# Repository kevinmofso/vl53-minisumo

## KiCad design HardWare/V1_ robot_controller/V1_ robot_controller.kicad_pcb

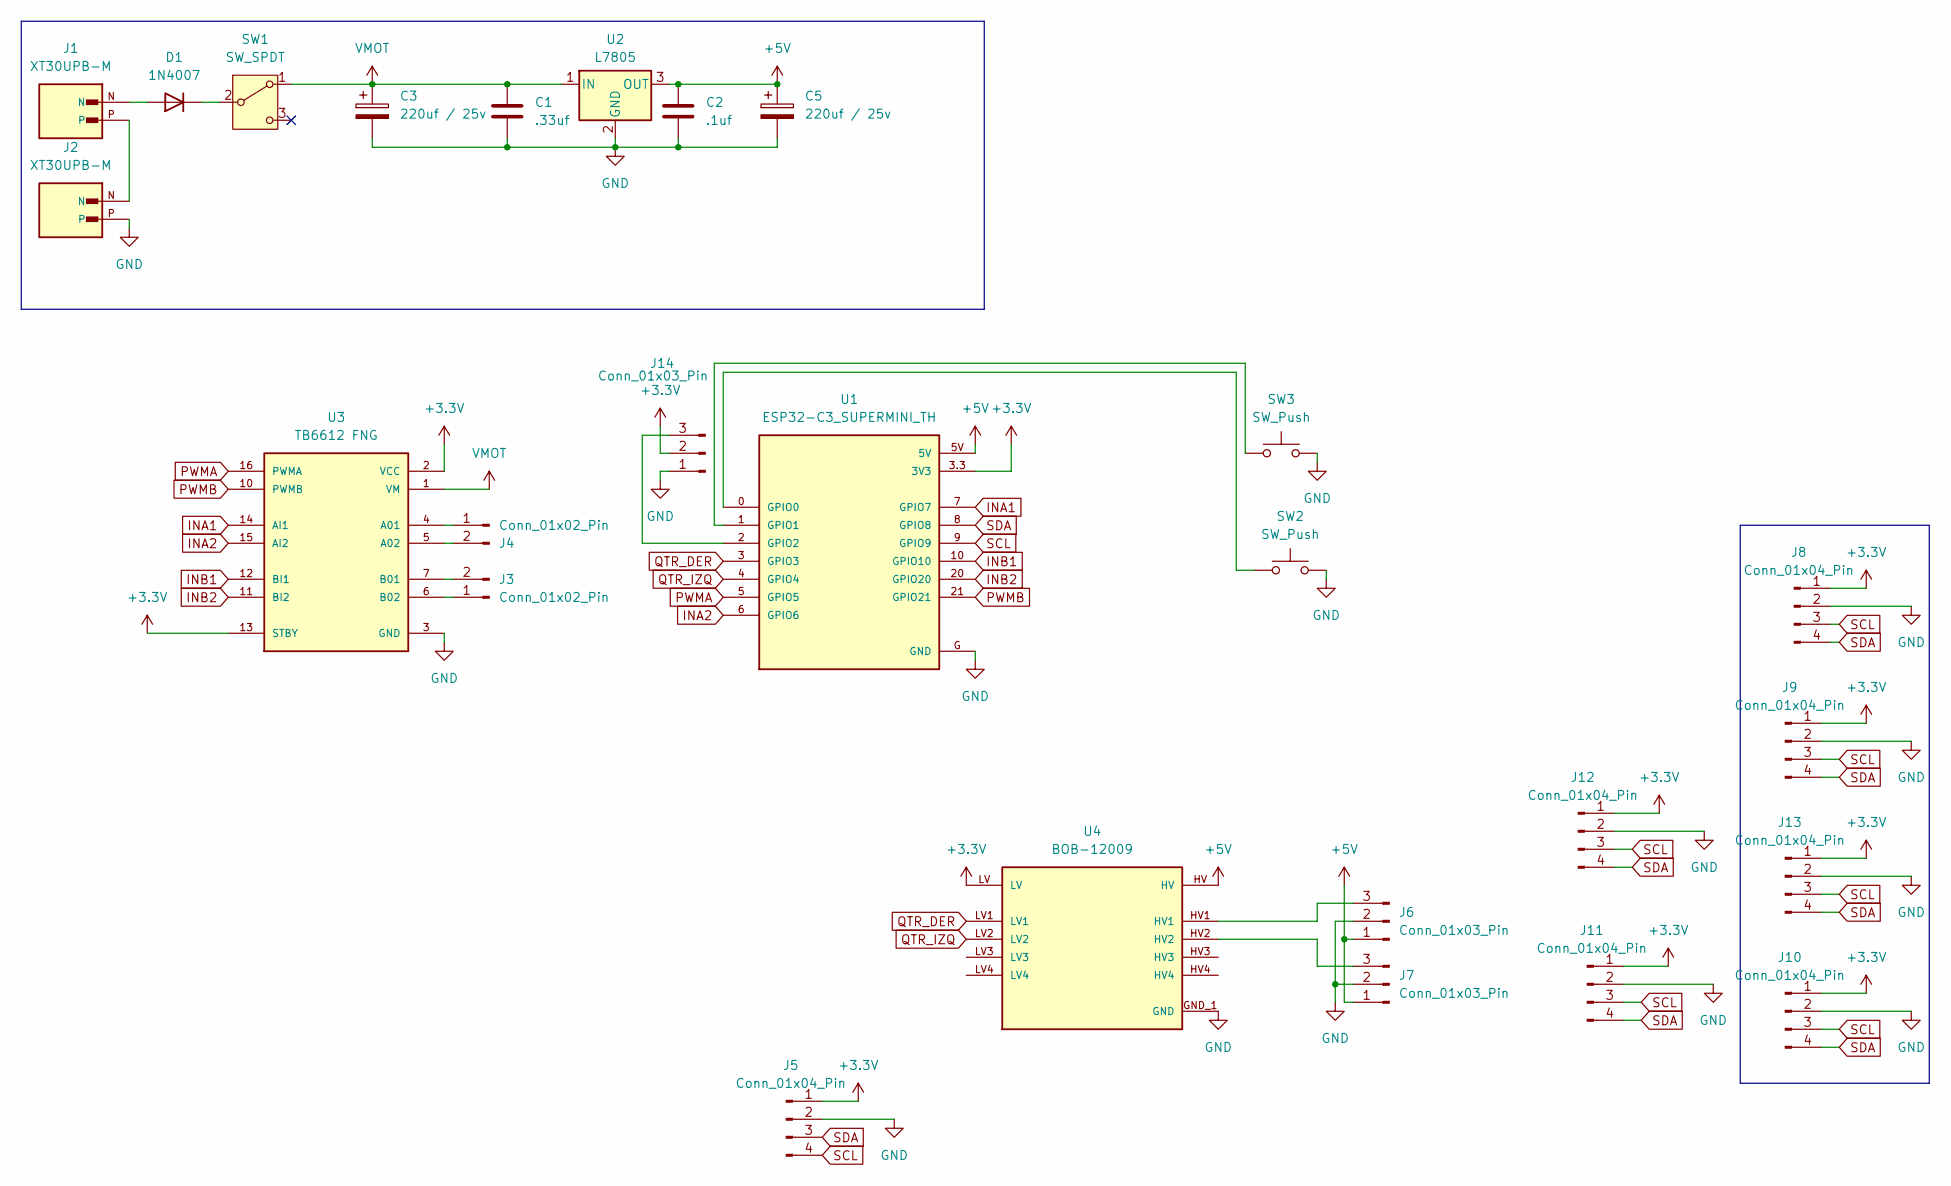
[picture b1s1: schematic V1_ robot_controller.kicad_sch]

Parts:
C1: .33uf; C_Disc_D3.0mm_W2.0mm_P2.50mm
C2: .1uf; C_Disc_D3.0mm_W2.0mm_P2.50mm
C3, C5: 220uf / 25v; CP_Radial_D6.3mm_P2.50mm
D1: 1N4007; D_DO-41_SOD81_P10.16mm_Horizontal
J1, J2: XT30UPB-M; AMASS_XT30UPB-M
J3, J4: Conn_01x02_Pin; Molex_KK-254_AE-6410-02A_1x02_P2.54mm_Vertical
J5, J8, J9, J10, J11, J12, J13: Conn_01x04_Pin; PinHeader_1x04_P2.54mm_Vertical
J6, J7, J14: Conn_01x03_Pin; PinHeader_1x03_P2.54mm_Vertical
SW1: SW_SPDT; SW_Slide_SPDT_Straight_CK_OS102011MS2Q
SW2, SW3: SW_Push; SW_PUSH_6mm_H4.3mm
U1: ESP32-C3_SUPERMINI_TH; MODULE_ESP32-C3_SUPERMINI_TH
U2: L7805; TO-220F-3_Horizontal_TabUp
U3: TB6612 FNG; MODULE_ROB-14450; PARTREV 11-13-17
U4: BOB-12009; CONV_BOB-12009; PARTREV 01

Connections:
+3.3V: J5.1, J8.1, J9.1, J10.1, J11.1, J12.1, J13.1, J14.2, U1.3.3 (3V3), U3.2 (VCC), U3.13 (STBY), U4.LV
+5V: C2.1, C5.1, J6.1, J7.1, U1.5V, U2.3 (OUT), U4.HV
GND: C1.2, C2.2, C3.2, C5.2, J2.P, J5.2, J6.2, J7.2, J8.2, J9.2, J10.2, J11.2, J12.2, J13.2, J14.1, SW2.1, SW3.1, U1.G (GND), U2.2 (GND), U3.3 (GND), U3.8 (GND), U3.9 (GND), U4.GND_1 (GND), U4.GND_2 (GND)
INA1: U1.7 (GPIO7), U3.14 (AI1)
INA2: U1.6 (GPIO6), U3.15 (AI2)
INB1: U1.10 (GPIO10), U3.12 (BI1)
INB2: U1.20 (GPIO20), U3.11 (BI2)
unnamed: D1.2 (A), J1.N
unnamed: D1.1 (K), SW1.2 (B)
unnamed: J1.P, J2.N
unnamed: J3.1, U3.6 (B02)
unnamed: J3.2, U3.7 (B01)
unnamed: J4.1, U3.4 (A01)
unnamed: J4.2, U3.5 (A02)
unnamed: J6.3, U4.HV1
unnamed: J7.3, U4.HV2
unnamed: J14.3, U1.2 (GPIO2)
unnamed: SW2.2, U1.0 (GPIO0)
unnamed: SW3.2, U1.1 (GPIO1)
PWMA: U1.5 (GPIO5), U3.16 (PWMA)
PWMB: U1.21 (GPIO21), U3.10 (PWMB)
QTR_DER: U1.3 (GPIO3), U4.LV1
QTR_IZQ: U1.4 (GPIO4), U4.LV2
SCL: J5.4, J8.3, J9.3, J10.3, J11.3, J12.3, J13.3, U1.9 (GPIO9)
SDA: J5.3, J8.4, J9.4, J10.4, J11.4, J12.4, J13.4, U1.8 (GPIO8)
VMOT: C1.1, C3.1, SW1.1 (A), U2.1 (IN), U3.1 (VM)

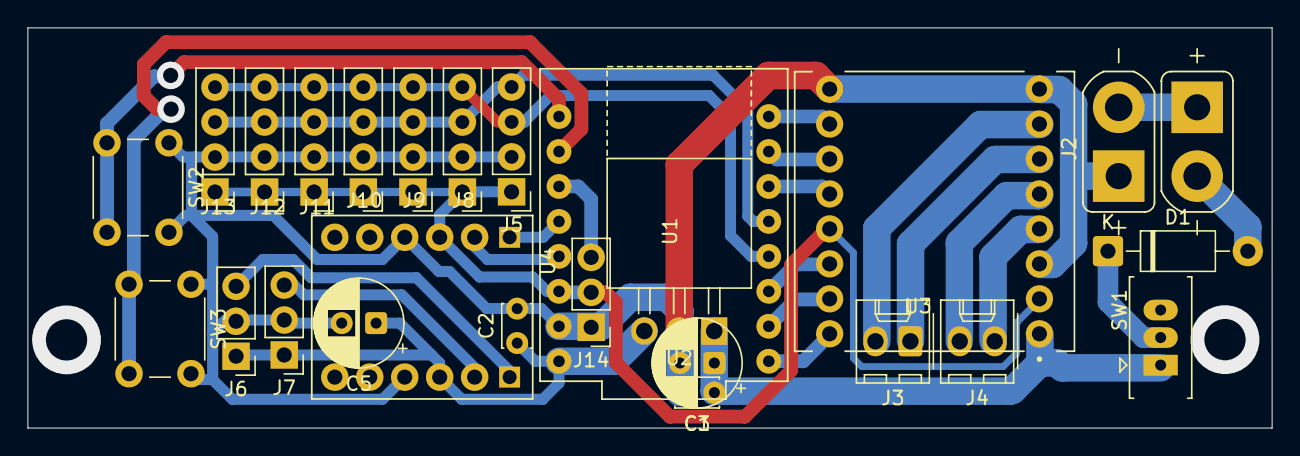
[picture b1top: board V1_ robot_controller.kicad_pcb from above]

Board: 2 copper layers, 90.4 x 29.1 mm, 26 parts (0 on the bottom side), 26 nets.

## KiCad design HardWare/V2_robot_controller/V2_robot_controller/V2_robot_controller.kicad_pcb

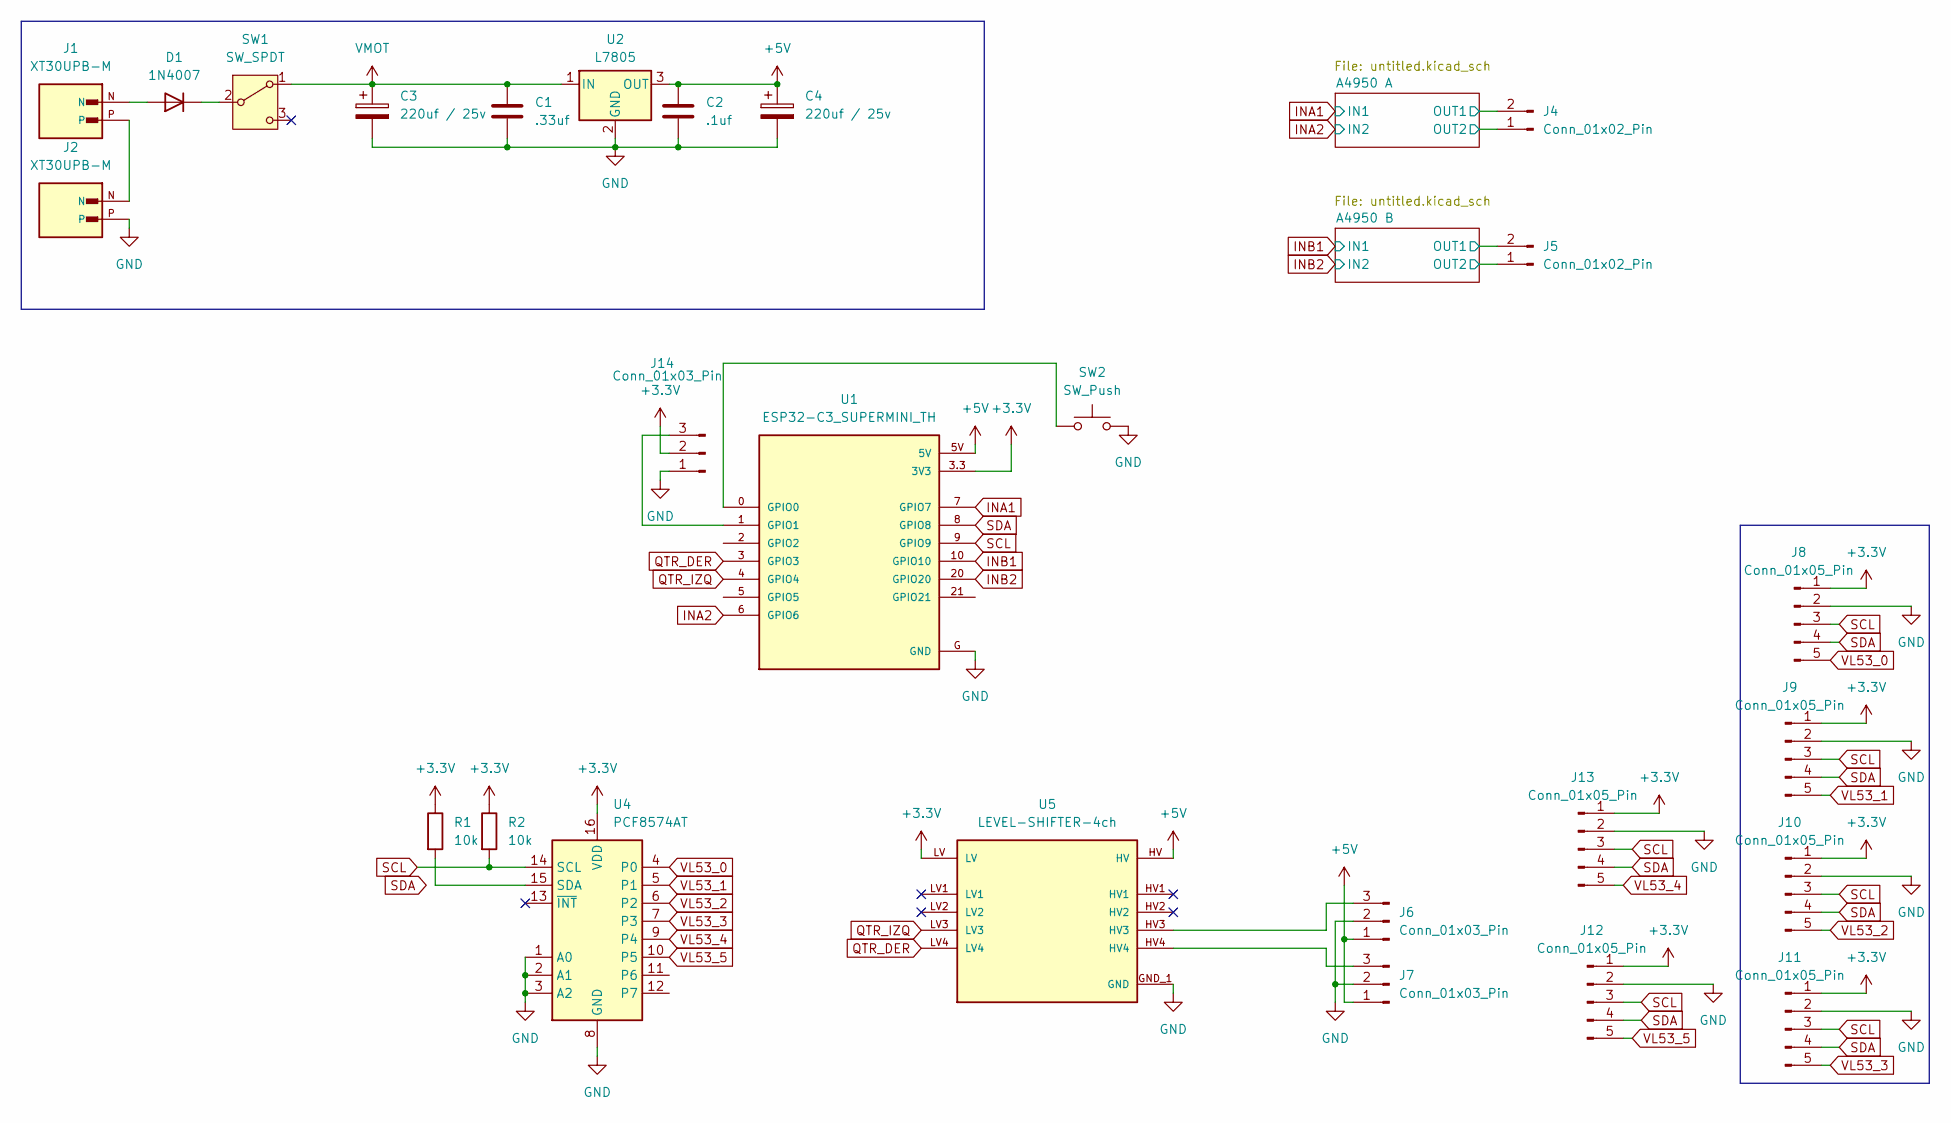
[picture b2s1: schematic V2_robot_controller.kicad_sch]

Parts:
C1: .33uf; C_Disc_D3.0mm_W2.0mm_P2.50mm
C2: .1uf; C_Disc_D3.0mm_W2.0mm_P2.50mm
C3: 220uf / 25v; CP_Radial_D6.3mm_P2.50mm
C4: 220uf / 25v; CP_Radial_D8.0mm_P3.80mm
D1: 1N4007; D_DO-41_SOD81_P10.16mm_Horizontal
J1, J2: XT30UPB-M; AMASS_XT30UPB-M
J4, J5: Conn_01x02_Pin; Molex_KK-254_AE-6410-02A_1x02_P2.54mm_Vertical
J6, J7, J14: Conn_01x03_Pin; PinHeader_1x03_P2.54mm_Vertical
J8, J9, J10, J11, J12, J13: Conn_01x05_Pin; PinHeader_1x05_P2.54mm_Vertical
R1, R2: 10k; R_0805_2012Metric_Pad1.20x1.40mm_HandSolder
SW1: SW_SPDT; SW_Slide_SPDT_Straight_CK_OS102011MS2Q
SW2: SW_Push; SW_PUSH_6mm_H4.3mm
U1: ESP32-C3_SUPERMINI_TH; MODULE_ESP32-C3_SUPERMINI_TH
U2: L7805; TO-220F-3_Horizontal_TabUp
U4: PCF8574AT; SOIC-16W_7.5x10.3mm_P1.27mm
U5: LEVEL-SHIFTER-4ch; CONV_BOB-12009; PARTREV 01

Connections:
+3.3V: J8.1, J9.1, J10.1, J11.1, J12.1, J13.1, J14.2, R1.1, R2.1, U1.3.3 (3V3), U4.16 (VDD), U5.LV; also elsewhere on the board
+5V: C2.1, C4.1, J6.1, J7.1, U1.5V, U2.3 (OUT), U5.HV
/A4950 A/OUT1: J4.2; also elsewhere on the board
/A4950 A/OUT2: J4.1; also elsewhere on the board
/A4950 B/OUT1: J5.2; also elsewhere on the board
/A4950 B/OUT2: J5.1; also elsewhere on the board
GND: C1.2, C2.2, C3.2, C4.2, J2.P, J6.2, J7.2, J8.2, J9.2, J10.2, J11.2, J12.2, J13.2, J14.1, SW2.1, U1.G (GND), U2.2 (GND), U4.1 (A0), U4.2 (A1), U4.3 (A2), U4.8 (GND), U5.GND_1 (GND), U5.GND_2 (GND); also elsewhere on the board
INA1: U1.7 (GPIO7); also elsewhere on the board
INA2: U1.6 (GPIO6); also elsewhere on the board
INB1: U1.10 (GPIO10); also elsewhere on the board
INB2: U1.20 (GPIO20); also elsewhere on the board
unnamed: D1.2 (A), J1.N
unnamed: D1.1 (K), SW1.2 (B)
unnamed: J1.P, J2.N
unnamed: J6.3, U5.HV3
unnamed: J7.3, U5.HV4
unnamed: J14.3, U1.1 (GPIO1)
unnamed: SW2.2, U1.0 (GPIO0)
unnamed: R1.2, U4.15 (SDA)
QTR_DER: U1.3 (GPIO3), U5.LV4
QTR_IZQ: U1.4 (GPIO4), U5.LV3
SCL: J8.3, J9.3, J10.3, J11.3, J12.3, J13.3, R2.2, U1.9 (GPIO9), U4.14 (SCL)
SDA: J8.4, J9.4, J10.4, J11.4, J12.4, J13.4, U1.8 (GPIO8)
VL53_0: J8.5, U4.4 (P0)
VL53_1: J9.5, U4.5 (P1)
VL53_2: J10.5, U4.6 (P2)
VL53_3: J11.5, U4.7 (P3)
VL53_4: J13.5, U4.9 (P4)
VL53_5: J12.5, U4.10 (P5)
VMOT: C1.1, C3.1, SW1.1 (A), U2.1 (IN); also elsewhere on the board

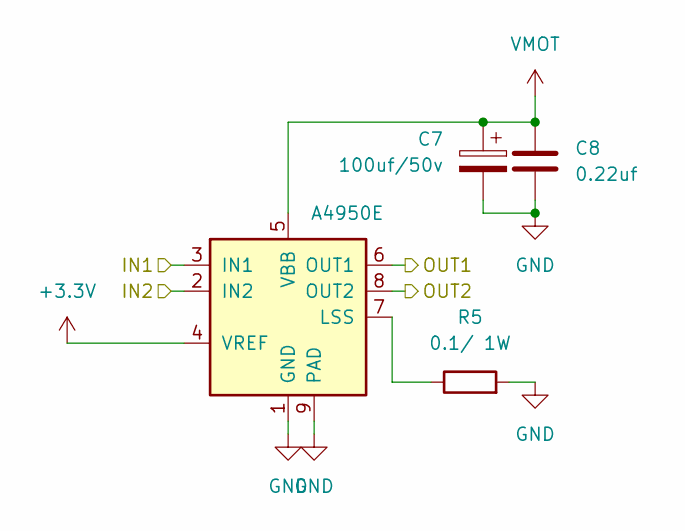
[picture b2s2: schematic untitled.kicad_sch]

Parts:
C7: 100uf/50v; CP_Radial_D8.0mm_P3.50mm
C8: 0.22uf; C_0805_2012Metric_Pad1.18x1.45mm_HandSolder
R5: 0.1/ 1W; R_Axial_DIN0204_L3.6mm_D1.6mm_P7.62mm_Horizontal
U7: A4950E; SOIC-8-1EP_3.9x4.9mm_P1.27mm_EP2.41x3.3mm

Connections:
+3.3V: U7.4 (VREF); also elsewhere on the board
/A4950 A/OUT1: U7.6 (OUT1); also elsewhere on the board
/A4950 A/OUT2: U7.8 (OUT2); also elsewhere on the board
GND: C7.2, C8.2, R5.2, U7.1 (GND), U7.9 (PAD); also elsewhere on the board
INA1: U7.3 (IN1); also elsewhere on the board
INA2: U7.2 (IN2); also elsewhere on the board
unnamed: R5.1, U7.7 (LSS)
VMOT: C7.1, C8.1, U7.5 (VBB); also elsewhere on the board

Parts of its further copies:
C9: 100uf/50v; CP_Radial_D8.0mm_P3.50mm
C10: 0.22uf; C_0805_2012Metric_Pad1.18x1.45mm_HandSolder
R6: 0.1/ 1W; R_Axial_DIN0204_L3.6mm_D1.6mm_P7.62mm_Horizontal
U8: A4950E; SOIC-8-1EP_3.9x4.9mm_P1.27mm_EP2.41x3.3mm

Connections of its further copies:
+3.3V: U8.4 (VREF); also elsewhere on the board
/A4950 B/OUT1: U8.6 (OUT1); also elsewhere on the board
/A4950 B/OUT2: U8.8 (OUT2); also elsewhere on the board
GND: C9.2, C10.2, R6.2, U8.1 (GND), U8.9 (PAD); also elsewhere on the board
INB1: U8.3 (IN1); also elsewhere on the board
INB2: U8.2 (IN2); also elsewhere on the board
unnamed: R6.1, U8.7 (LSS)
VMOT: C9.1, C10.1, U8.5 (VBB); also elsewhere on the board

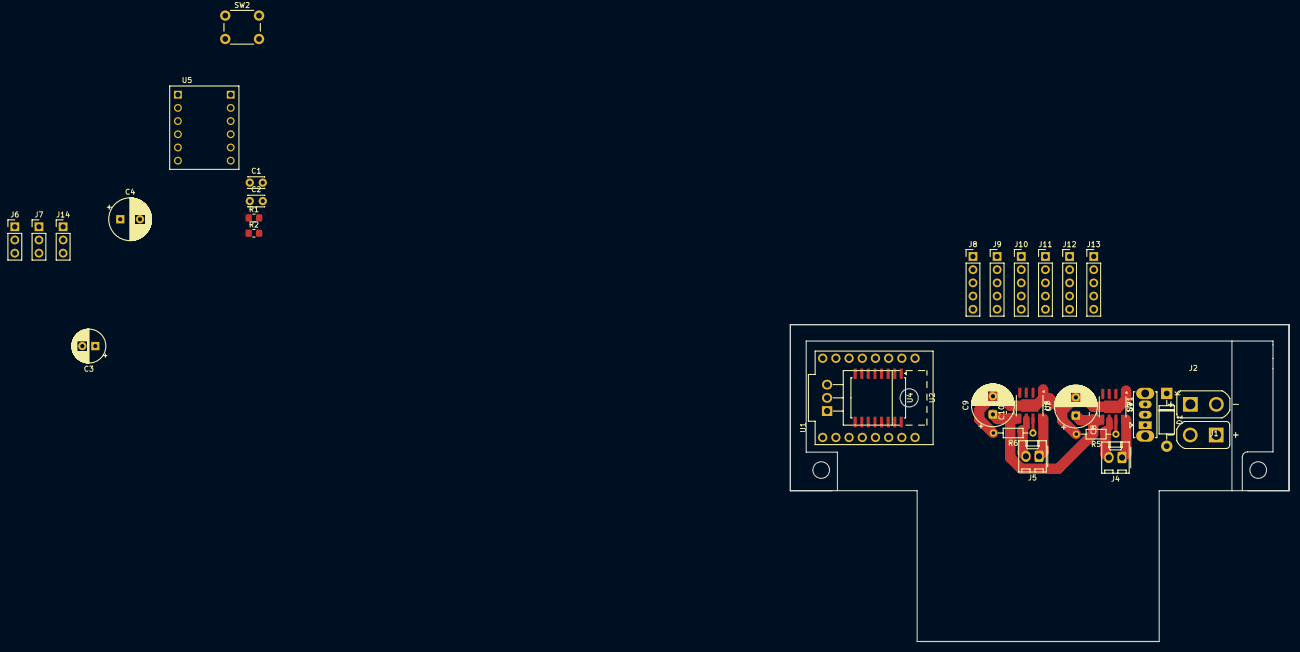
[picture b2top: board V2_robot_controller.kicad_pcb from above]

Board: 2 copper layers, 96.0 x 61.0 mm, 34 parts (0 on the bottom side), 32 nets.

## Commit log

2026-01-04 pruebas y librerias
2026-01-05 3d
    3d
2026-01-07 falta sensor de piso
    -logica de sensor de piso y reaccion a los bordes
    - estrategias
    - angulo de incio
2026-01-07 actualizacion de librerias
    agregue la libreria para el control ir
2026-01-07 g
    g
2026-01-19 d
    d
2026-01-19 t
    t
2026-01-19 1
    1
2026-01-23 kicad
    empece el diseño en kicad
2026-01-28 m,
    jkgh
2026-01-29 orden y processing
    orden y processing
2026-01-30 modelo 3d del pcb en el diseño
    agregue al diseño del minisumo el modelo 3d de la pcb
2026-02-16 r
    r
